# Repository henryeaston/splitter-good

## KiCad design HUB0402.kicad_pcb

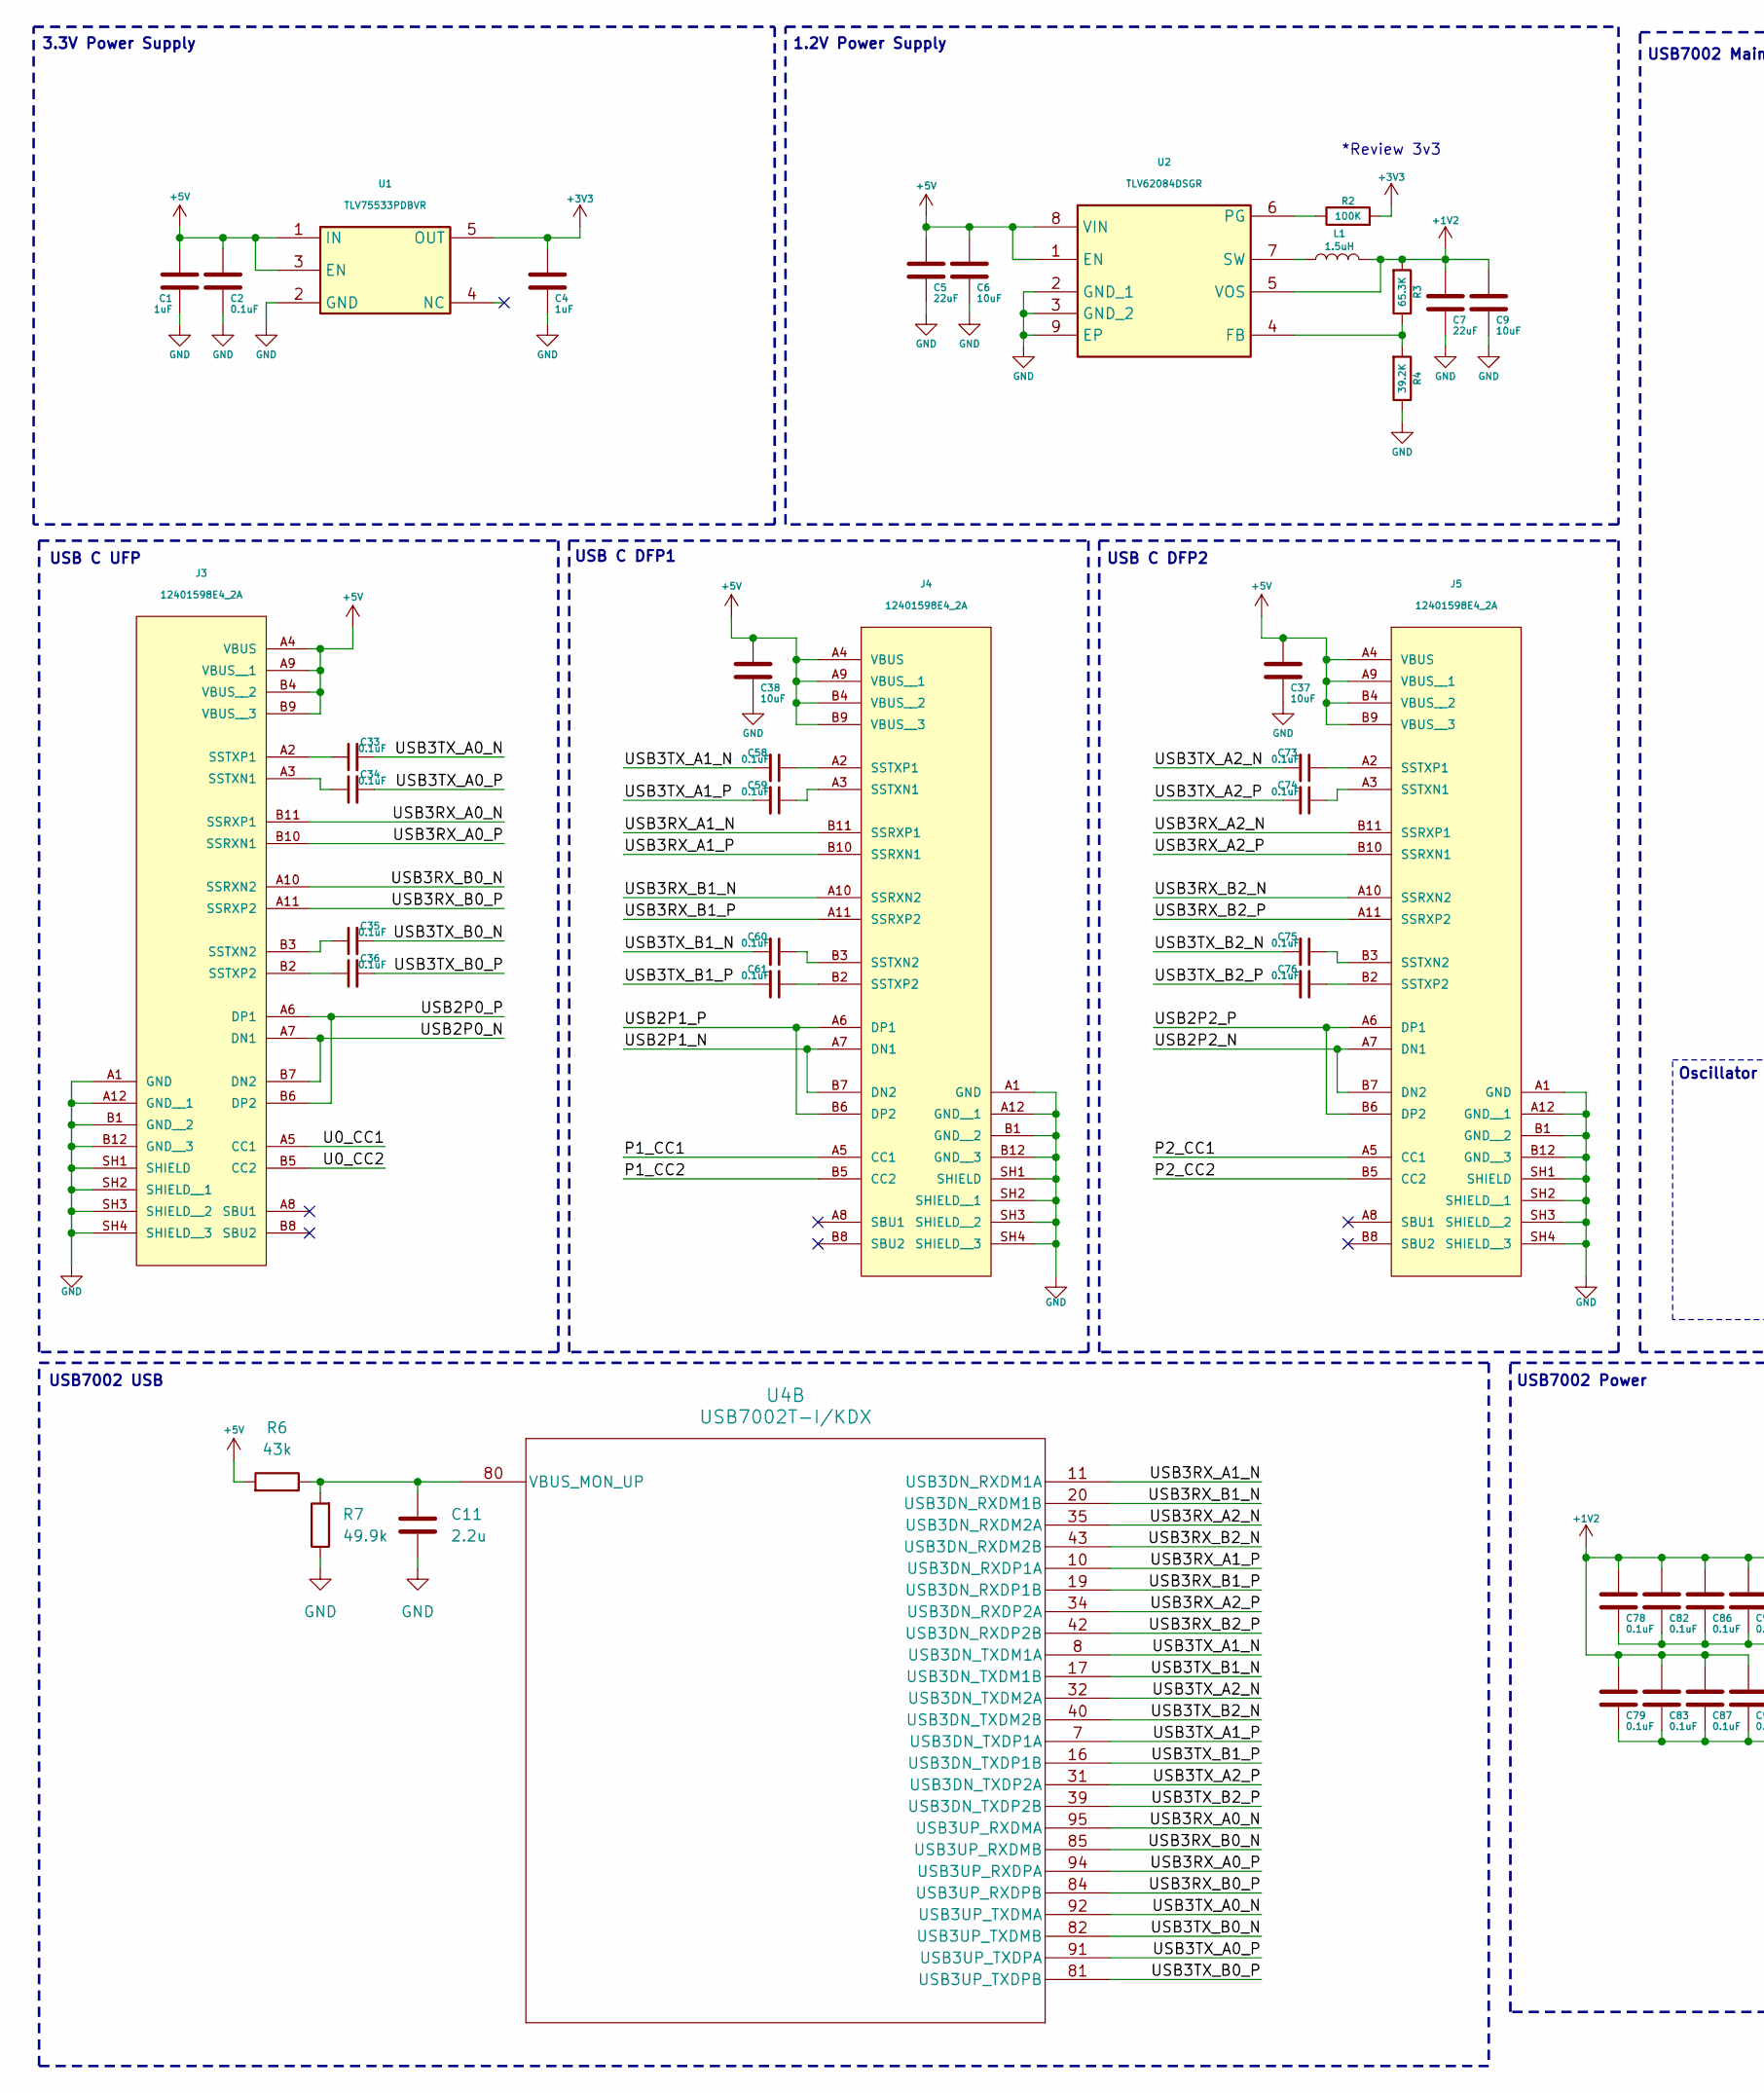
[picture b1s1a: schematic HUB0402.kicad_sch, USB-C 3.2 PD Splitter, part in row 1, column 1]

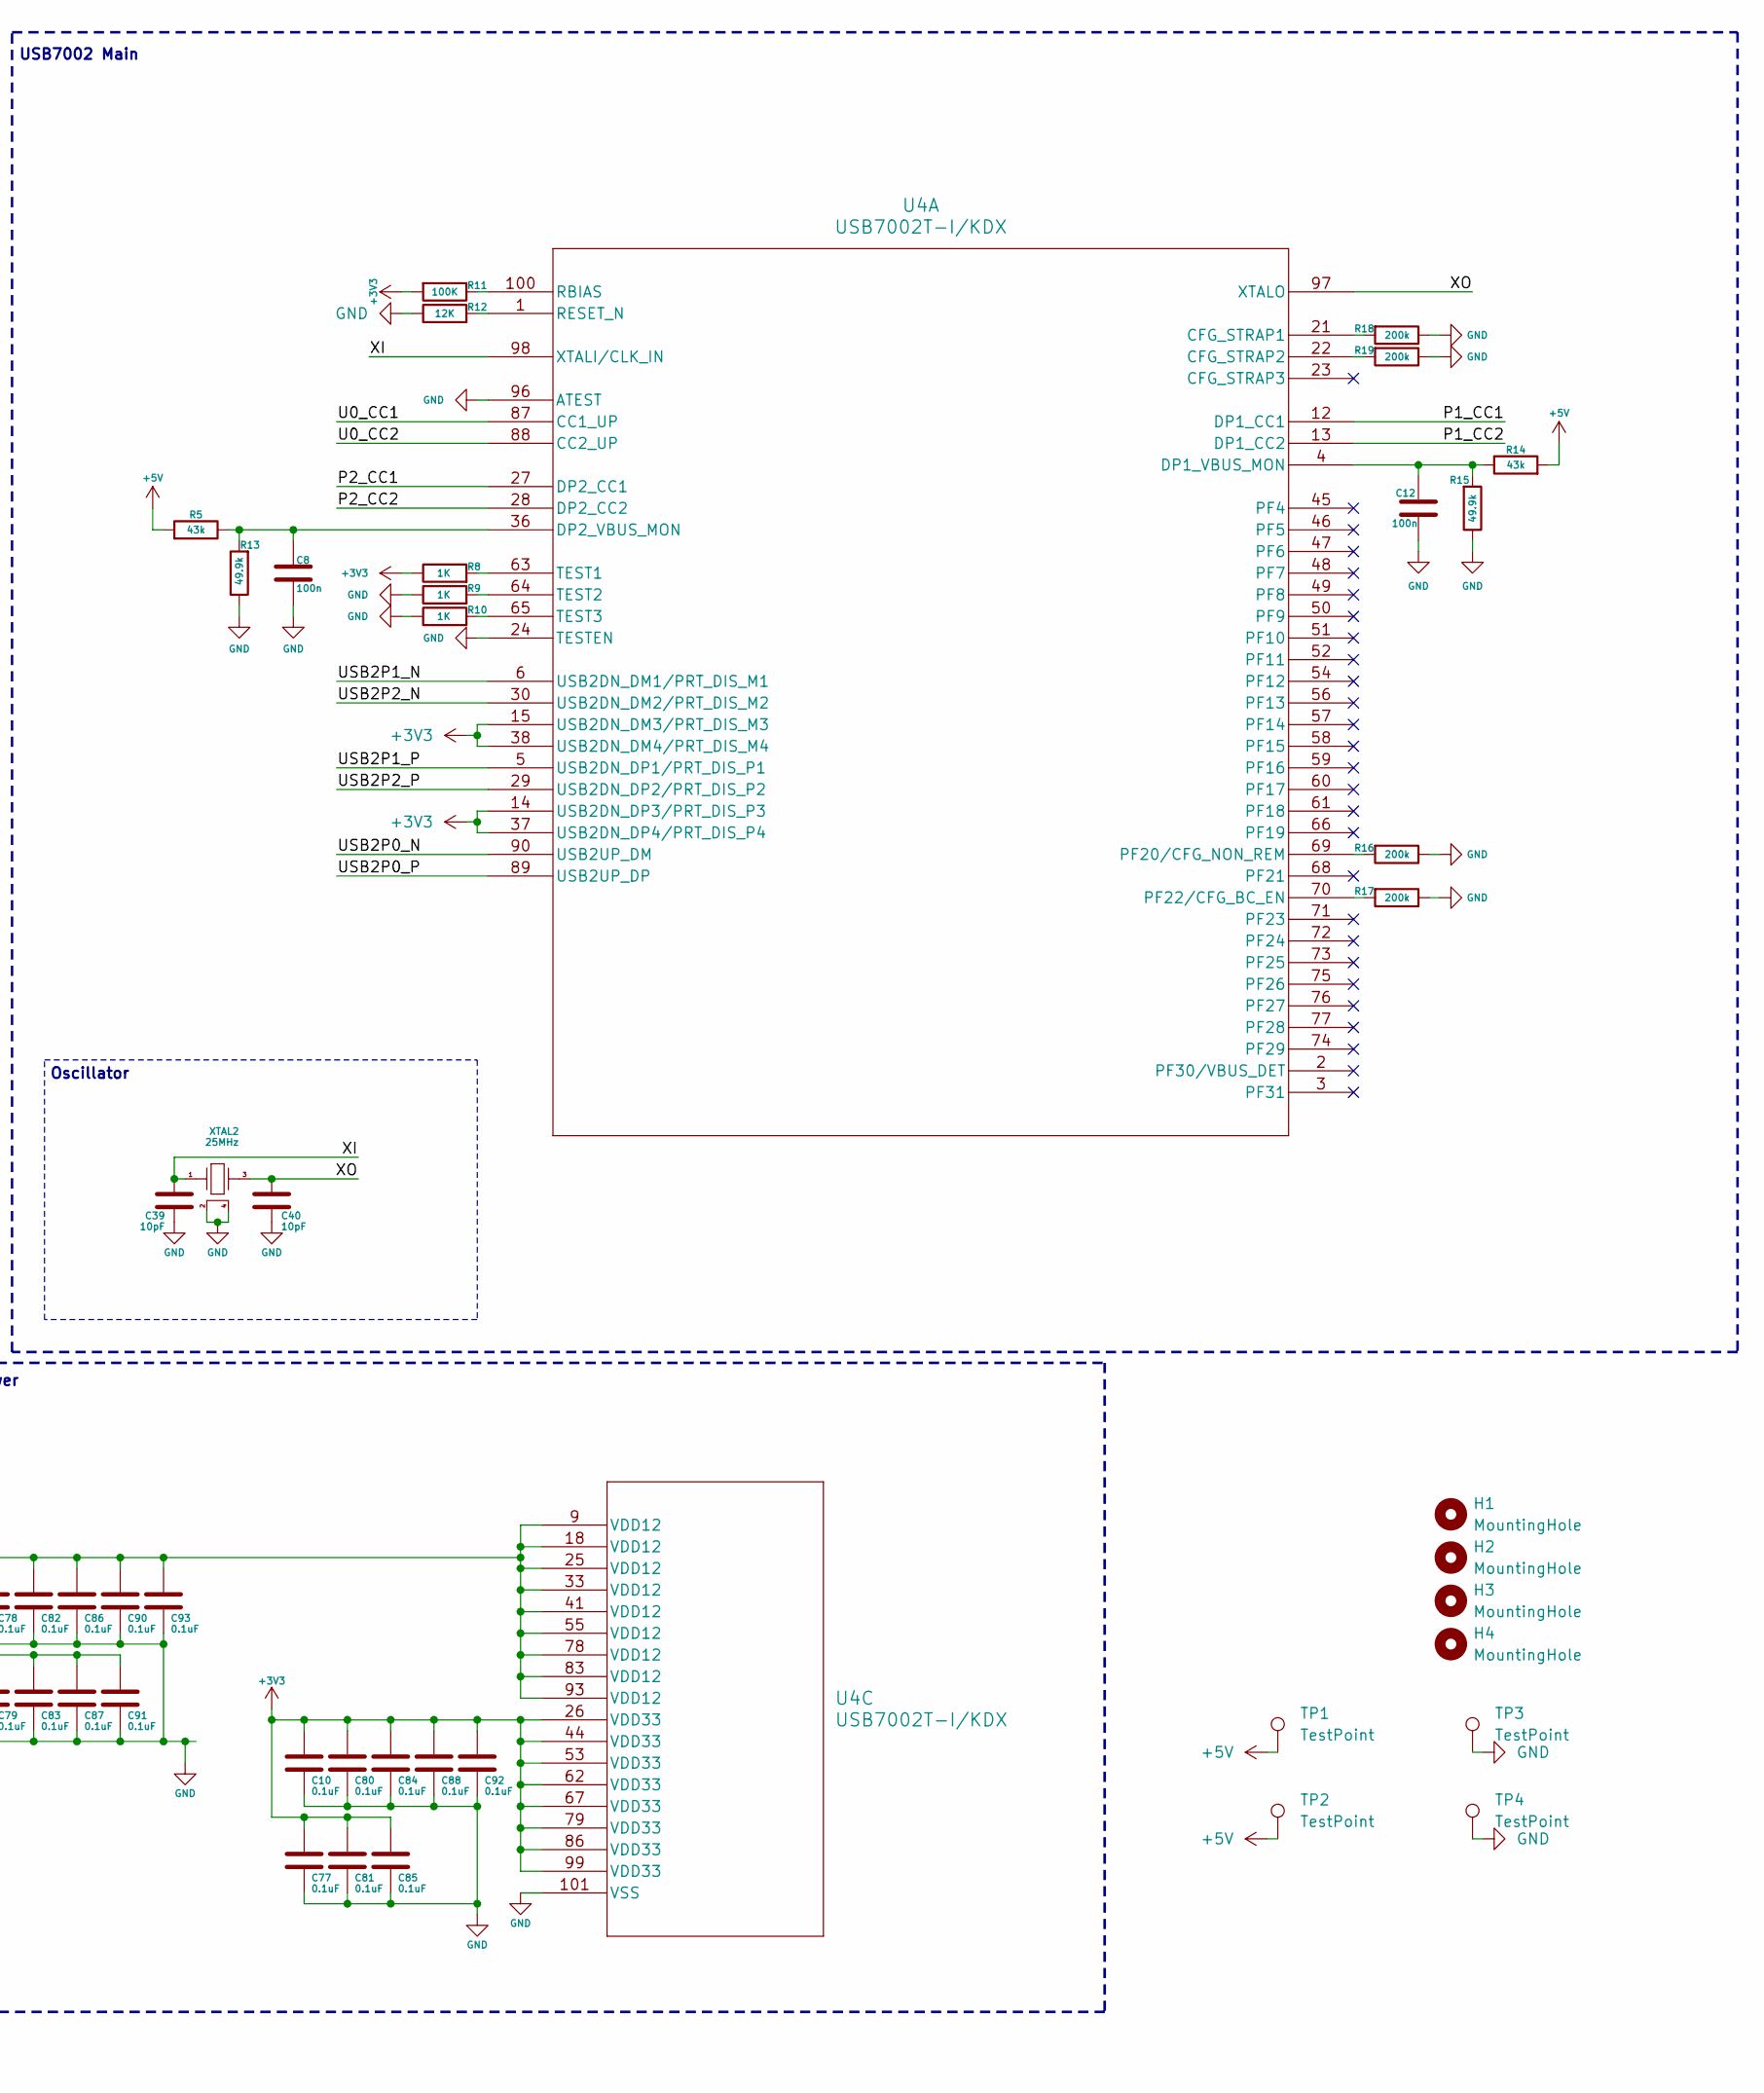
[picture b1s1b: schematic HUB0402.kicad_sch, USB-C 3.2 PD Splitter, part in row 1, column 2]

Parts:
C1, C4: 1uF; C_0402_1005Metric
C2, C10, C33, C34, C35, C36, C58, C59, C60, C61, C73, C74, C75, C76, C77, C78, C79, C80, C81, C82, C83, C84, C85, C86, C87, C88, C90, C91, C92, C93: 0.1uF; C_0402_1005Metric
C5, C7: 22uF; C_0603_1608Metric
C6, C9: 10uF; C_0603_1608Metric
C8, C12: 100n; C_0402_1005Metric
C11: 2.2u; C_0402_1005Metric
C37, C38: 10uF; C_0402_1005Metric
C39, C40: 10pF; C_0402_1005Metric
H1, H2, H3, H4: MountingHole; MountingHole_2.2mm_M2
J3, J4, J5: 12401598E4_2A; TYPE-C-SMD_918-418K2022Y40003; PARTREV 4
L1: 1.5uH; L_1210_3225Metric_Pad1.42x2.65mm_HandSolder
R2, R11: 100K; R_0402_1005Metric
R3: 65.3K; R_0402_1005Metric
R4: 39.2K; R_0402_1005Metric
R5, R6, R14: 43k; R_0402_1005Metric
R7, R13, R15: 49.9k; R_0402_1005Metric
R8, R9, R10: 1K; R_0402_1005Metric; MFR.Part # 0603WAF1001T5E; LCSC Part # C21190
R12: 12K; R_0402_1005Metric
R16, R17, R18, R19: 200k; R_0402_1005Metric; MFR.Part # 0603WAF1001T5E; LCSC Part # C21190
TP1, TP2, TP3, TP4: TestPoint; TestPoint_Pad_D1.5mm
U1: TLV75533PDBVR; SOT-23-5; Mouser Part Number 595-TLV75533PDBVR
U2: TLV62084DSGR; WSON-8-1EP_2x2mm_P0.5mm_EP0.9x1.6mm_ThermalVias; Mouser Part Number 595-TLV62084DSGR
U4: USB7002T-I/KDX; VQFN-100-1EP_12x12mm_P0.4mm_EP8x8mm
XTAL2: 25MHz; Crystal_SMD_Abracon_ABM8G-4Pin_3.2x2.5mm

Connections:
+1V2: C7.1, C9.1, C78.1, C79.1, C82.1, C83.1, C86.1, C87.1, C90.1, C91.1, C93.1, L1.2, R3.2, U2.5 (VOS), U4.9 (VDD12), U4.18 (VDD12), U4.25 (VDD12), U4.33 (VDD12), U4.41 (VDD12), U4.55 (VDD12), U4.78 (VDD12), U4.83 (VDD12), U4.93 (VDD12)
+3V3: C4.1, C10.1, C77.1, C80.1, C81.1, C84.1, C85.1, C88.1, C92.1, R2.2, R8.1, R11.2, U1.5 (OUT), U4.14 (USB2DN_DP3/PRT_DIS_P3), U4.15 (USB2DN_DM3/PRT_DIS_M3), U4.26 (VDD33), U4.37 (USB2DN_DP4/PRT_DIS_P4), U4.38 (USB2DN_DM4/PRT_DIS_M4), U4.44 (VDD33), U4.53 (VDD33), U4.62 (VDD33), U4.67 (VDD33), U4.79 (VDD33), U4.86 (VDD33), U4.99 (VDD33)
+5V: C1.1, C2.1, C5.1, C6.1, C37.1, C38.1, J3.A4 (VBUS), J3.A9 (VBUS__1), J3.B4 (VBUS__2), J3.B9 (VBUS__3), J4.A4 (VBUS), J4.A9 (VBUS__1), J4.B4 (VBUS__2), J4.B9 (VBUS__3), J5.A4 (VBUS), J5.A9 (VBUS__1), J5.B4 (VBUS__2), J5.B9 (VBUS__3), R5.2, R6.2, R14.2, TP1.1, TP2.1, U1.1 (IN), U1.3 (EN), U2.1 (EN), U2.8 (VIN)
/P1_CC1: J4.A5 (CC1), U4.12 (DP1_CC1)
/P1_CC2: J4.B5 (CC2), U4.13 (DP1_CC2)
/P2_CC1: J5.A5 (CC1), U4.27 (DP2_CC1)
/P2_CC2: J5.B5 (CC2), U4.28 (DP2_CC2)
/U0_CC1: J3.A5 (CC1), U4.87 (CC1_UP)
/U0_CC2: J3.B5 (CC2), U4.88 (CC2_UP)
/USB2P0_N: J3.A7 (DN1), J3.B7 (DN2), U4.90 (USB2UP_DM)
/USB2P0_P: J3.A6 (DP1), J3.B6 (DP2), U4.89 (USB2UP_DP)
/USB2P1_N: J4.A7 (DN1), J4.B7 (DN2), U4.6 (USB2DN_DM1/PRT_DIS_M1)
/USB2P1_P: J4.A6 (DP1), J4.B6 (DP2), U4.5 (USB2DN_DP1/PRT_DIS_P1)
/USB2P2_N: J5.A7 (DN1), J5.B7 (DN2), U4.30 (USB2DN_DM2/PRT_DIS_M2)
/USB2P2_P: J5.A6 (DP1), J5.B6 (DP2), U4.29 (USB2DN_DP2/PRT_DIS_P2)
/USB3RX_A0_N: J3.B11 (SSRXP1), U4.95 (USB3UP_RXDMA)
/USB3RX_A0_P: J3.B10 (SSRXN1), U4.94 (USB3UP_RXDPA)
/USB3RX_A1_N: J4.B11 (SSRXP1), U4.11 (USB3DN_RXDM1A)
/USB3RX_A1_P: J4.B10 (SSRXN1), U4.10 (USB3DN_RXDP1A)
/USB3RX_A2_N: J5.B11 (SSRXP1), U4.35 (USB3DN_RXDM2A)
/USB3RX_A2_P: J5.B10 (SSRXN1), U4.34 (USB3DN_RXDP2A)
/USB3RX_B0_N: J3.A10 (SSRXN2), U4.85 (USB3UP_RXDMB)
/USB3RX_B0_P: J3.A11 (SSRXP2), U4.84 (USB3UP_RXDPB)
/USB3RX_B1_N: J4.A10 (SSRXN2), U4.20 (USB3DN_RXDM1B)
/USB3RX_B1_P: J4.A11 (SSRXP2), U4.19 (USB3DN_RXDP1B)
/USB3RX_B2_N: J5.A10 (SSRXN2), U4.43 (USB3DN_RXDM2B)
/USB3RX_B2_P: J5.A11 (SSRXP2), U4.42 (USB3DN_RXDP2B)
/USB3TX_A0_N: C33.2, U4.92 (USB3UP_TXDMA)
/USB3TX_A0_P: C34.2, U4.91 (USB3UP_TXDPA)
/USB3TX_A1_N: C58.2, U4.8 (USB3DN_TXDM1A)
/USB3TX_A1_P: C59.2, U4.7 (USB3DN_TXDP1A)
/USB3TX_A2_N: C73.2, U4.32 (USB3DN_TXDM2A)
/USB3TX_A2_P: C74.2, U4.31 (USB3DN_TXDP2A)
/USB3TX_B0_N: C35.2, U4.82 (USB3UP_TXDMB)
/USB3TX_B0_P: C36.2, U4.81 (USB3UP_TXDPB)
/USB3TX_B1_N: C60.2, U4.17 (USB3DN_TXDM1B)
/USB3TX_B1_P: C61.2, U4.16 (USB3DN_TXDP1B)
/USB3TX_B2_N: C75.2, U4.40 (USB3DN_TXDM2B)
/USB3TX_B2_P: C76.2, U4.39 (USB3DN_TXDP2B)
/XI: C39.1, U4.98 (XTALI/CLK_IN), XTAL2.1
/XO: C40.1, U4.97 (XTALO), XTAL2.3
GND: C1.2, C2.2, C4.2, C5.2, C6.2, C7.2, C8.2, C9.2, C10.2, C11.2, C12.2, C37.2, C38.2, C39.2, C40.2, C77.2, C78.2, C79.2, C80.2, C81.2, C82.2, C83.2, C84.2, C85.2, C86.2, C87.2, C88.2, C90.2, C91.2, C92.2, C93.2, J3.A1 (GND), J3.A12 (GND__1), J3.B1 (GND__2), J3.B12 (GND__3), J3.SH1 (SHIELD), J3.SH2 (SHIELD__1), J3.SH3 (SHIELD__2), J3.SH4 (SHIELD__3), J4.A1 (GND), J4.A12 (GND__1), J4.B1 (GND__2), J4.B12 (GND__3), J4.SH1 (SHIELD), J4.SH2 (SHIELD__1), J4.SH3 (SHIELD__2), J4.SH4 (SHIELD__3), J5.A1 (GND), J5.A12 (GND__1), J5.B1 (GND__2), J5.B12 (GND__3), J5.SH1 (SHIELD), J5.SH2 (SHIELD__1), J5.SH3 (SHIELD__2), J5.SH4 (SHIELD__3), R4.1, R7.1, R9.1, R10.1, R12.1, R13.1, R15.1, R16.1, R17.1, R18.1, R19.1, TP3.1, TP4.1, U1.2 (GND), U2.2 (GND_1), U2.3 (GND_2), U2.9 (EP), U4.24 (TESTEN), U4.96 (ATEST), U4.101 (VSS), XTAL2.2, XTAL2.4
unnamed: C34.1, J3.A3 (SSTXN1)
unnamed: C35.1, J3.B3 (SSTXN2)
unnamed: C33.1, J3.A2 (SSTXP1)
unnamed: C36.1, J3.B2 (SSTXP2)
unnamed: C59.1, J4.A3 (SSTXN1)
unnamed: C60.1, J4.B3 (SSTXN2)
unnamed: C58.1, J4.A2 (SSTXP1)
unnamed: C61.1, J4.B2 (SSTXP2)
unnamed: C74.1, J5.A3 (SSTXN1)
unnamed: C75.1, J5.B3 (SSTXN2)
unnamed: C73.1, J5.A2 (SSTXP1)
unnamed: C76.1, J5.B2 (SSTXP2)
unnamed: R3.1, R4.2, U2.4 (FB)
unnamed: R2.1, U2.6 (PG)
unnamed: L1.1, U2.7 (SW)
unnamed: R18.2, U4.21 (CFG_STRAP1)
unnamed: R19.2, U4.22 (CFG_STRAP2)
unnamed: C12.1, R14.1, R15.2, U4.4 (DP1_VBUS_MON)
unnamed: C8.1, R5.1, R13.2, U4.36 (DP2_VBUS_MON)
unnamed: R16.2, U4.69 (PF20/CFG_NON_REM)
unnamed: R17.2, U4.70 (PF22/CFG_BC_EN)
unnamed: R11.1, U4.100 (RBIAS)
unnamed: R12.2, U4.1 (RESET_N)
unnamed: R8.2, U4.63 (TEST1)
unnamed: R9.2, U4.64 (TEST2)
unnamed: R10.2, U4.65 (TEST3)
unnamed: C11.1, R6.1, R7.2, U4.80 (VBUS_MON_UP)

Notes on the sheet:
3.3V Power Supply
Oscillator
USB C UFP
USB C DFP2
USB C DFP1
USB7002 Main
*Review 3v3
USB7002 USB
USB7002 Power
1.2V Power Supply

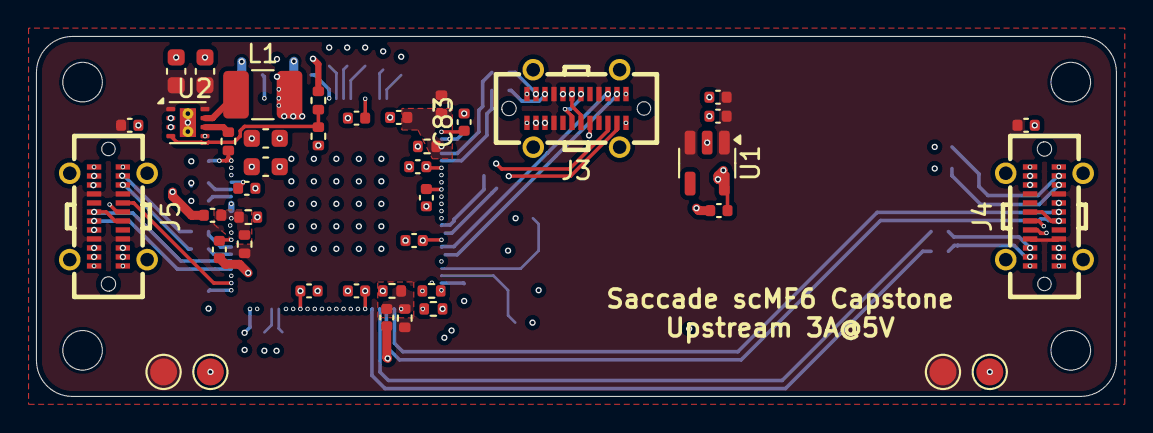
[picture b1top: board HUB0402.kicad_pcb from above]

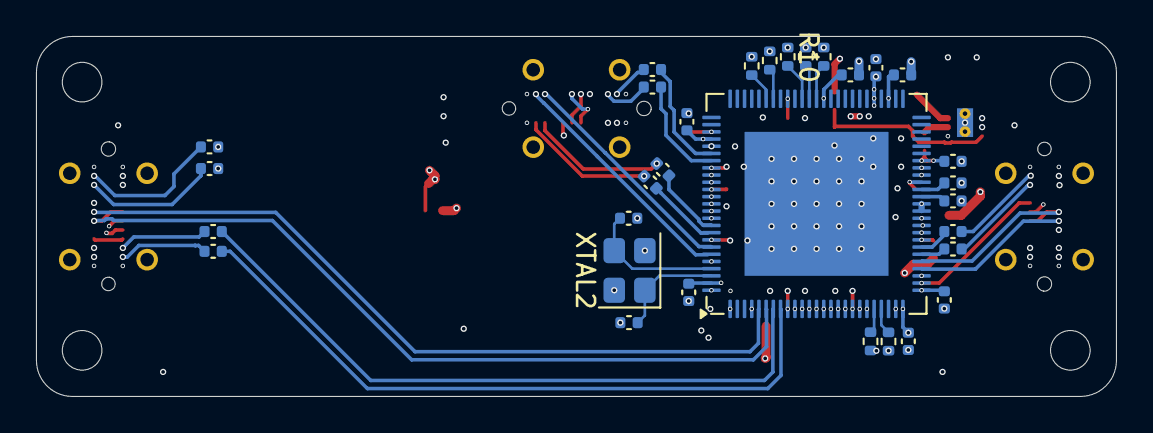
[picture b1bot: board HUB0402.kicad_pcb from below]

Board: 8 copper layers, 60.0 x 20.0 mm, 77 parts (31 on the bottom side), 69 nets.

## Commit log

2026-03-12 Starting Layout
2026-03-16 Layout mostly done
